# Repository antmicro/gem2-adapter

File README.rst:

GEM2 Adapter
============

Copyright (c) 2020 `Antmicro <https://www.antmicro.com>`_

.. image:: https://img.shields.io/badge/View%20on-Antmicro%20Open%20Source%20Portal-332d37?style=flat-square
      :target: https://github.com/antmicro/gem2-adapter
   
.. figure:: img/gem2-adapter.png

This repository contains PCB design files for an adapter board accommodating the GEM2 chip created jointly by `zGlue <http://zglue.com>`_ and `Antmicro <http://www.antmicro.com>`_.
The `GEM2 design <https://zglue.com/design-automation/oci/project/gem2>`_ utilizes the zGlue ZiP chiplet technology and has been prepared using zGlue's `ChipBuilder <http://chipbuilder.zglue.com/>`_ tool.
The design has been produced as a single integrated circuit in the LGA-96 package.

The GEM2 chip contains the following components located on a dynamically reconfigurable interposer:

* PicoRV32-based "Raven" RISC-V ASIC implementation (see `raven-picorv32 <https://github.com/efabless/raven-picorv32>`_ and associated resources)
* Lattice ``ICE40UP5K-UWG30ITR`` FPGA image processing
* 32Mbit SPI FLASH memory
* 12MHz system clock generator 
* Internal LDOs and power management unit maintaining 1V2, 1V8, 2V5, 3V3 system supplies

The chip is supplied from a single ``VUSB`` voltage of 5 VDC.
The board break-routes signals for MIPI Interfaces (Input and Output) along with Flash and FPGA programming pins and power supplies.

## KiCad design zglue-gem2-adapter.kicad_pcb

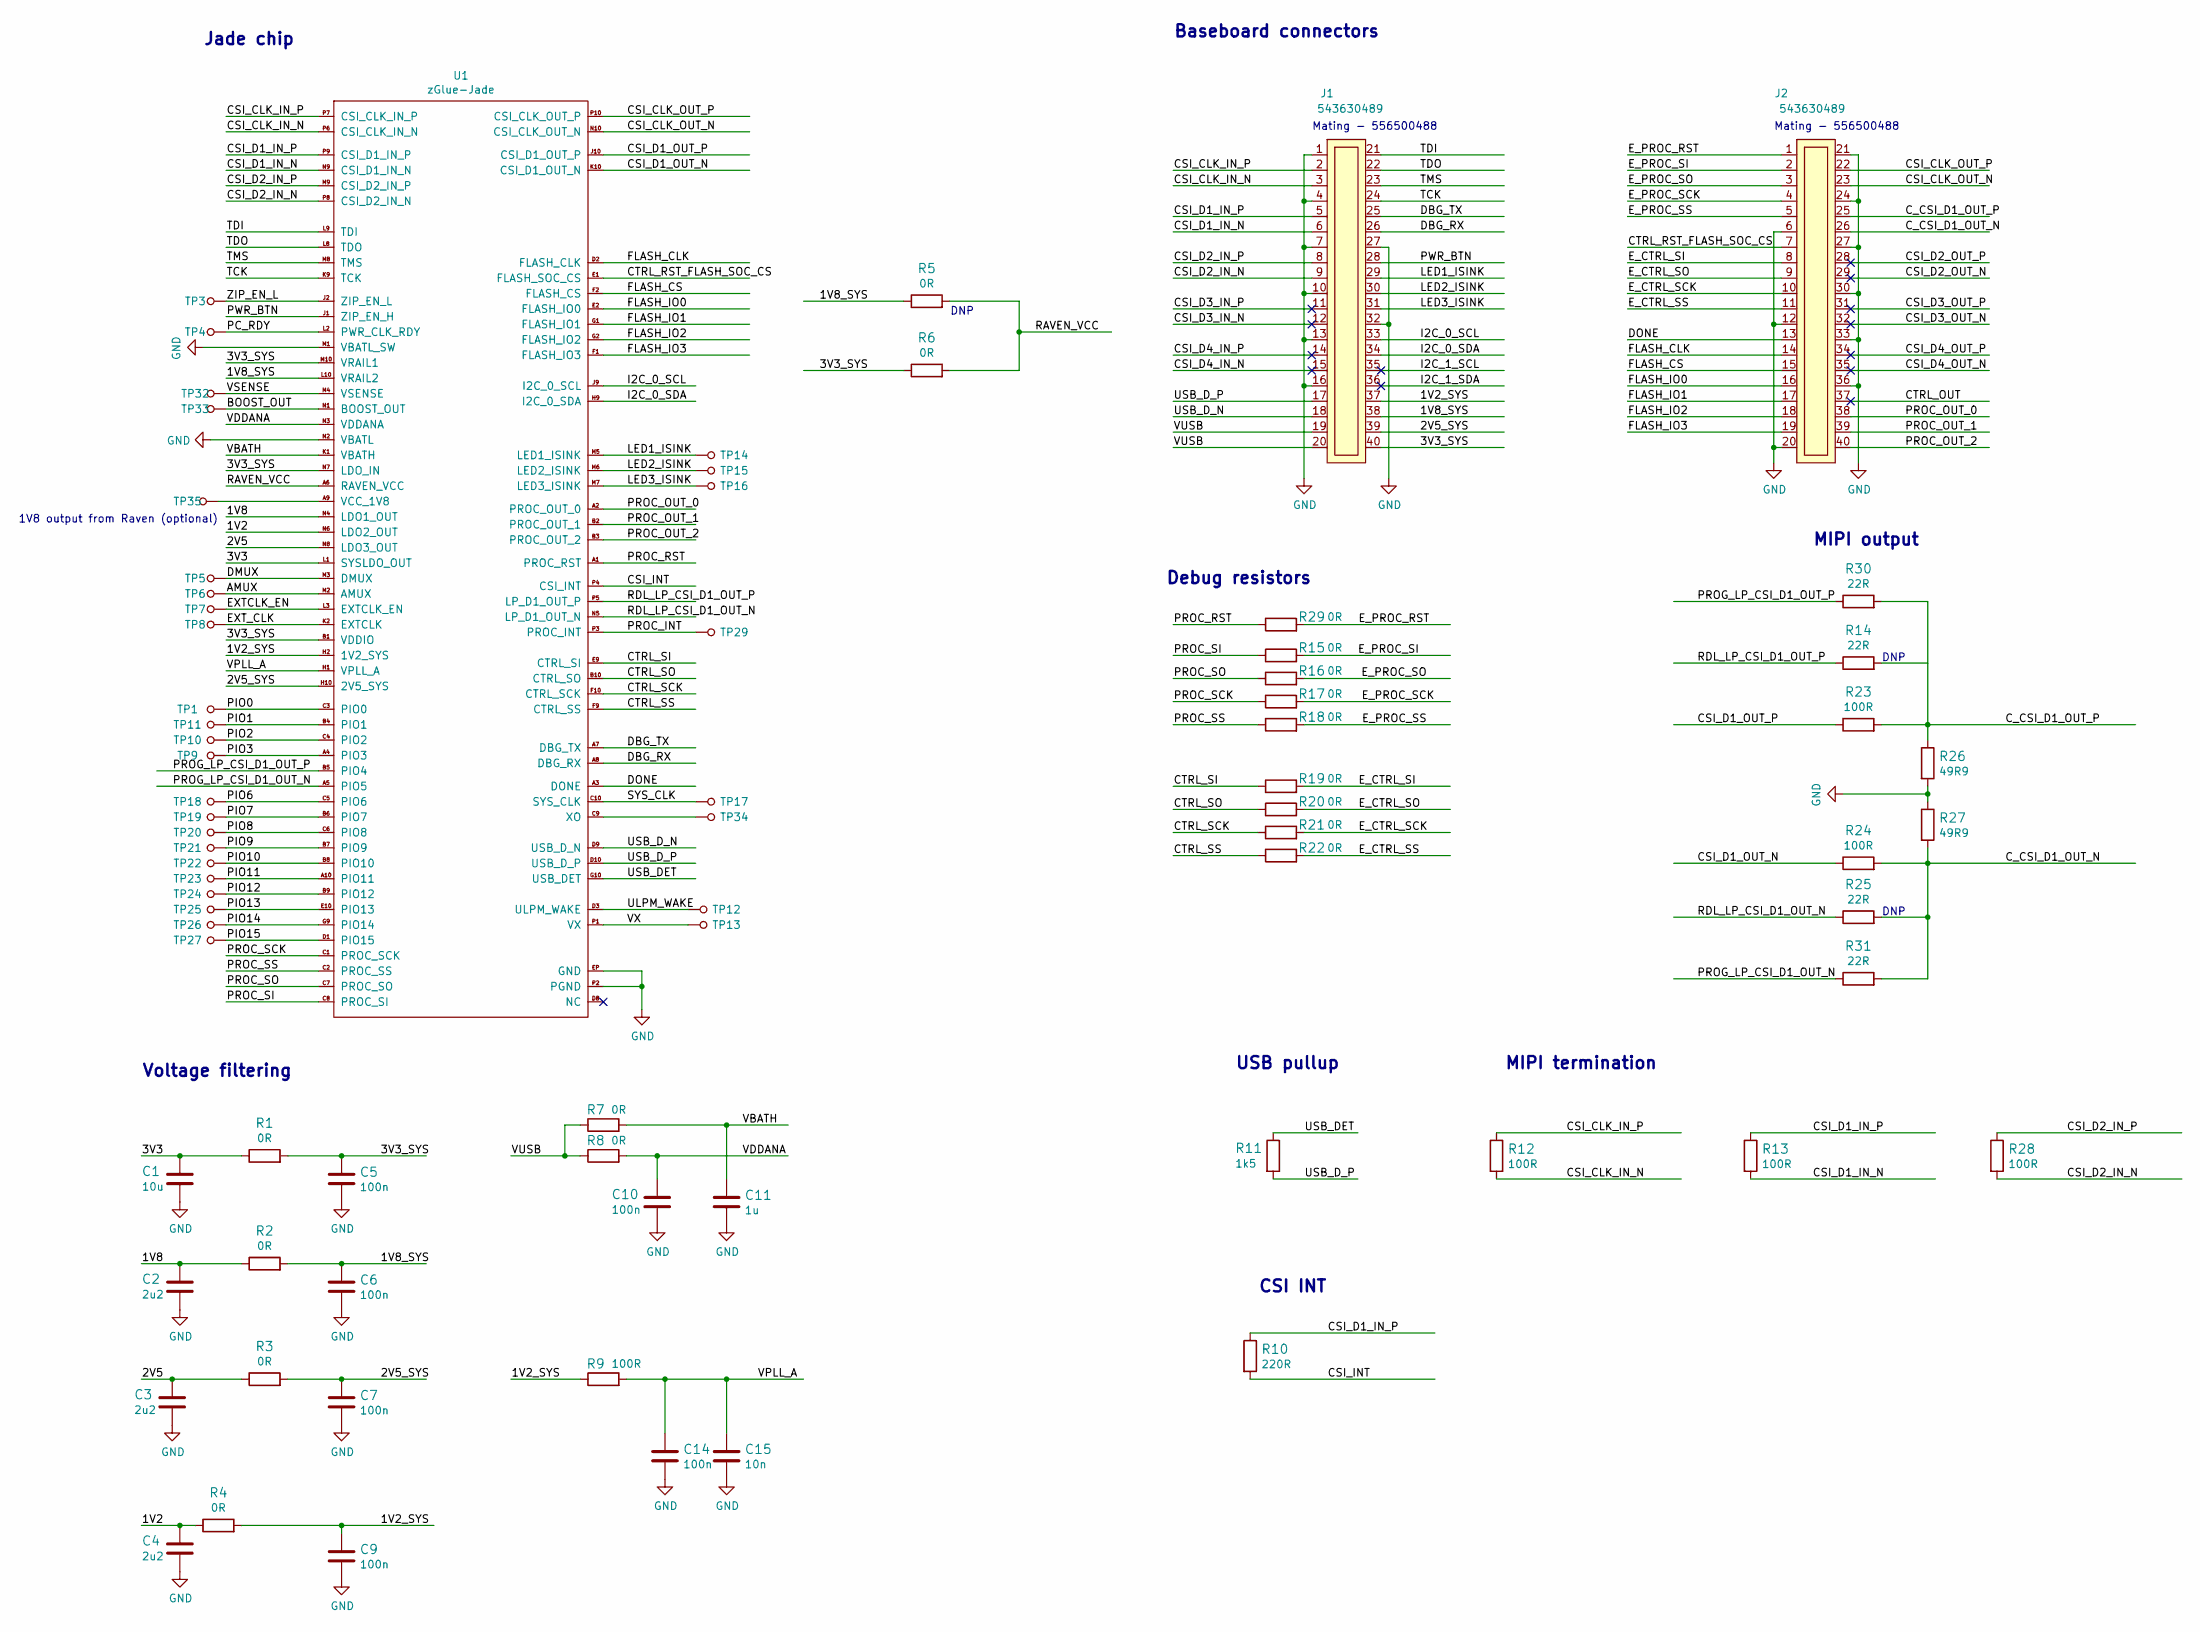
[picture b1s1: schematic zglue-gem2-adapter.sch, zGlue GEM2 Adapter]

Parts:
C1: C_10u_0402; 0402-cap; MPN C1005X5R0J106M050BC
C2, C3, C4: C_2u2_0402; 0402-cap; MPN C1005X5R1A225K050BC
C5, C6, C7, C9, C10, C14: C_100n_0402_6V3; 0402-cap; MPN 0402X104K6R3CT
C11: C_1u_0603; 0603-cap; MPN 0603X105K160CT
C15: C_10n_0402; 0402-cap; MPN 04025G103ZAT2A
J1, J2: 543630489; MPN 543630489
R1, R2, R3, R4, R5, R6, R7, R8, R15, R16, R17, R18, R19, R20, R21, R22, R29: R_0R_0402; 0402-res; MPN ERJ2GE0R00X
R9, R12, R13, R28: R_100R_0402; 0402-res; MPN CR0402-FX-1000GLF
R10: R_220R_0402; 0402-res; MPN CRG0402J220R
R11: R_1k5_0402; 0402-res; MPN ERJ2RKF1501X
R14, R25, R30, R31: R_22R_0402; 0402-res; MPN CRCW040222R0FKED
R23, R24: R_120R_0402; 0402-res; MPN CR0402-FX-1000GLF
R26, R27: R_49R9_0402; 0402-res; MPN CRCW040249R9FKED
TP1, TP3, TP4, TP5, TP6, TP7, TP8, TP9, TP10, TP11, TP12, TP13, TP14, TP15, TP16, TP17, TP18, TP19, TP20, TP21, TP22, TP23, TP24, TP25, TP26, TP27, TP29, TP32, TP33, TP34, TP35: TP_SMD1MM; Testpoint_smd_1mm
U1: zGlue-Jade; Z-Glue_LGA-96

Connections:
/1V2: C4.1, R4.1, U1.N6 (LDO2_OUT)
/1V2_SYS: C9.1, J1.37, R4.2, R9.1, U1.H2 (1V2_SYS)
/1V8: C2.1, R2.1, U1.N4 (LDO1_OUT)
/1V8_SYS: C6.1, J1.38, R2.2, R5.1, U1.L10 (VRAIL2)
/2V5: C3.1, R3.1, U1.N8 (LDO3_OUT)
/2V5_SYS: C7.1, J1.39, R3.2, U1.H10 (2V5_SYS)
/3V3: C1.1, R1.1, U1.L1 (SYSLDO_OUT)
/3V3_SYS: C5.1, J1.40, R1.2, R6.1, U1.B1 (VDDIO), U1.M10 (VRAIL1), U1.N7 (LDO_IN)
/AMUX: TP6.1, U1.M2 (AMUX)
/BOOST_OUT: TP33.1, U1.N1 (BOOST_OUT)
/CSI_CLK_IN_N: J1.3, R12.2, U1.P6 (CSI_CLK_IN_N)
/CSI_CLK_IN_P: J1.2, R12.1, U1.P7 (CSI_CLK_IN_P)
/CSI_CLK_OUT_N: J2.23, U1.N10 (CSI_CLK_OUT_N)
/CSI_CLK_OUT_P: J2.22, U1.P10 (CSI_CLK_OUT_P)
/CSI_D1_IN_N: J1.6, R13.2, U1.N9 (CSI_D1_IN_N)
/CSI_D1_IN_P: J1.5, R10.1, R13.1, U1.P9 (CSI_D1_IN_P)
/CSI_D1_OUT_N: R24.1, U1.K10 (CSI_D1_OUT_N)
/CSI_D1_OUT_P: R23.1, U1.J10 (CSI_D1_OUT_P)
/CSI_D2_IN_N: J1.9, R28.2, U1.P8 (CSI_D2_IN_N)
/CSI_D2_IN_P: J1.8, R28.1, U1.M9 (CSI_D2_IN_P)
/CSI_D2_OUT_N: J2.29
/CSI_D2_OUT_P: J2.28
/CSI_D3_IN_N: J1.12
/CSI_D3_IN_P: J1.11
/CSI_D3_OUT_N: J2.32
/CSI_D3_OUT_P: J2.31
/CSI_D4_IN_N: J1.15
/CSI_D4_IN_P: J1.14
/CSI_D4_OUT_N: J2.35
/CSI_D4_OUT_P: J2.34
/CSI_INT: R10.2, U1.P4 (CSI_INT)
/CTRL_OUT: J2.37
/CTRL_RST_FLASH_SOC_CS: J2.7, U1.E1 (FLASH_SOC_CS)
/CTRL_SCK: R21.1, U1.F10 (CTRL_SCK)
/CTRL_SI: R19.1, U1.E9 (CTRL_SI)
/CTRL_SO: R20.1, U1.B10 (CTRL_SO)
/CTRL_SS: R22.1, U1.F9 (CTRL_SS)
/C_CSI_D1_OUT_N: J2.26, R24.2, R25.2, R27.2, R31.2
/C_CSI_D1_OUT_P: J2.25, R14.2, R23.2, R26.1, R30.2
/DBG_RX: J1.26, U1.A8 (DBG_RX)
/DBG_TX: J1.25, U1.A7 (DBG_TX)
/DMUX: TP5.1, U1.M3 (DMUX)
/DONE: J2.13, U1.A3 (DONE)
/EXTCLK_EN: TP7.1, U1.L3 (EXTCLK_EN)
/EXT_CLK: TP8.1, U1.K2 (EXTCLK)
/E_CTRL_SCK: J2.10, R21.2
/E_CTRL_SI: J2.8, R19.2
/E_CTRL_SO: J2.9, R20.2
/E_CTRL_SS: J2.11, R22.2
/E_PROC_RST: J2.1, R29.2
/E_PROC_SCK: J2.4, R17.2
/E_PROC_SI: J2.2, R15.2
/E_PROC_SO: J2.3, R16.2
/E_PROC_SS: J2.5, R18.2
/FLASH_CLK: J2.14, U1.D2 (FLASH_CLK)
/FLASH_CS: J2.15, U1.F2 (FLASH_CS)
/FLASH_IO0: J2.16, U1.E2 (FLASH_IO0)
/FLASH_IO1: J2.17, U1.G1 (FLASH_IO1)
/FLASH_IO2: J2.18, U1.G2 (FLASH_IO2)
/FLASH_IO3: J2.19, U1.F1 (FLASH_IO3)
/I2C_0_SCL: J1.33, U1.J9 (I2C_0_SCL)
/I2C_0_SDA: J1.34, U1.H9 (I2C_0_SDA)
/I2C_1_SCL: J1.35
/I2C_1_SDA: J1.36
/LED1_ISINK: J1.29, TP14.1, U1.M5 (LED1_ISINK)
/LED2_ISINK: J1.30, TP15.1, U1.M6 (LED2_ISINK)
/LED3_ISINK: J1.31, TP16.1, U1.M7 (LED3_ISINK)
/PC_RDY: TP4.1, U1.L2 (PWR_CLK_RDY)
/PIO0: TP1.1, U1.C3 (PIO0)
/PIO1: TP11.1, U1.B4 (PIO1)
/PIO2: TP10.1, U1.C4 (PIO2)
/PIO3: TP9.1, U1.A4 (PIO3)
/PIO6: TP18.1, U1.C5 (PIO6)
/PIO7: TP19.1, U1.B6 (PIO7)
/PIO8: TP20.1, U1.C6 (PIO8)
/PIO9: TP21.1, U1.B7 (PIO9)
/PIO10: TP22.1, U1.B8 (PIO10)
/PIO11: TP23.1, U1.A10 (PIO11)
/PIO12: TP24.1, U1.B9 (PIO12)
/PIO13: TP25.1, U1.E10 (PIO13)
/PIO14: TP26.1, U1.G9 (PIO14)
/PIO15: TP27.1, U1.D1 (PIO15)
/PROC_INT: TP29.1, U1.P3 (PROC_INT)
/PROC_OUT_0: J2.38, U1.A2 (PROC_OUT_0)
/PROC_OUT_1: J2.39, U1.B2 (PROC_OUT_1)
/PROC_OUT_2: J2.40, U1.B3 (PROC_OUT_2)
/PROC_RST: R29.1, U1.A1 (PROC_RST)
/PROC_SCK: R17.1, U1.C1 (PROC_SCK)
/PROC_SI: R15.1, U1.C8 (PROC_SI)
/PROC_SO: R16.1, U1.C7 (PROC_SO)
/PROC_SS: R18.1, U1.C2 (PROC_SS)
/PROG_LP_CSI_D1_OUT_N: R31.1, U1.A5 (PIO5)
/PROG_LP_CSI_D1_OUT_P: R30.1, U1.B5 (PIO4)
/PWR_BTN: J1.28, U1.J1 (ZIP_EN_H)
/RAVEN_VCC: R5.2, R6.2, U1.A6 (RAVEN_VCC)
/RDL_LP_CSI_D1_OUT_N: R25.1, U1.N5 (LP_D1_OUT_N)
/RDL_LP_CSI_D1_OUT_P: R14.1, U1.P5 (LP_D1_OUT_P)
/SYS_CLK: TP17.1, U1.C10 (SYS_CLK)
/TCK: J1.24, U1.K9 (TCK)
/TDI: J1.21, U1.L9 (TDI)
/TDO: J1.22, U1.L8 (TDO)
/TMS: J1.23, U1.M8 (TMS)
/ULPM_WAKE: TP12.1, U1.D3 (ULPM_WAKE)
/USB_DET: R11.1, U1.G10 (USB_DET)
/USB_D_N: J1.18, U1.D9 (USB_D_N)
/USB_D_P: J1.17, R11.2, U1.D10 (USB_D_P)
/VBATH: C11.1, R7.2, U1.K1 (VBATH)
/VDDANA: C10.1, R8.2, U1.N3 (VDDANA)
/VPLL_A: C14.1, C15.1, R9.2, U1.H1 (VPLL_A)
/VSENSE: TP32.1, U1.M4 (VSENSE)
/VUSB: J1.19, J1.20, R7.1, R8.1
/VX: TP13.1, U1.P1 (VX)
/ZIP_EN_L: TP3.1, U1.J2 (ZIP_EN_L)
GND: C1.2, C2.2, C3.2, C4.2, C5.2, C6.2, C7.2, C9.2, C10.2, C11.2, C14.2, C15.2, J1.1, J1.4, J1.7, J1.10, J1.13, J1.16, J1.27, J1.32, J2.6, J2.12, J2.20, J2.21, J2.24, J2.27, J2.30, J2.33, J2.36, R26.2, R27.1, U1.EP (GND), U1.M1 (VBATL_SW), U1.N2 (VBATL), U1.P2 (PGND)
unnamed: TP34.1, U1.C9 (XO)
unnamed: TP35.1, U1.A9 (VCC_1V8)

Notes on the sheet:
Jade chip
Voltage filtering
Mating - 556500488
Baseboard connectors
Debug resistors
USB pullup
1V8 output from Raven (optional)
MIPI termination
CSI INT
MIPI output
DNP

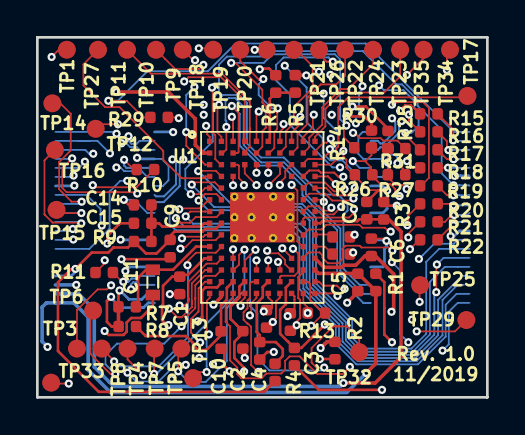
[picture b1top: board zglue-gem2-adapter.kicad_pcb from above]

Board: 6 copper layers, 25.0 x 20.0 mm, 77 parts (0 on the bottom side), 103 nets.

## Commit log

2020-05-29 Add component placement
2020-05-29 Add README
2020-05-29 Add LGA-96 step model, fix library links
2020-05-29 Rotate PCB by 180 deg to match chip logo orientation
2020-05-29 Move C1,2,3,4 closer to LDOs' outputs
2020-05-29 Modify LGA-96 thermal pad on paste layer
2020-05-29 Add initial layout
2020-05-29 Tune differential pairs
2020-05-29 Minor tweaks
2020-05-29 Add CSI_LP and CSI_INT signals and corresponding resistors
2020-05-29 Add 3D Vis to README
2020-05-29 Add DNP annotations
2020-05-29 Update pinout and layout
2020-05-29 Update the grid origin
2020-05-29 Add resistors for choosing CSI_LP signals connection
2020-05-29 Regenerate libraries
2020-05-29 Make more space on schematic sheet
2020-05-29 Update PCB
2020-05-29 Add logotype
2020-05-29 Update library naming
2020-05-29 Update GEM2 symbol
2020-05-29 README updates
2020-05-29 Review README
2020-05-29 Update PDF schematic
2020-10-01 Update photo
2020-10-01 Add OCI link
2020-10-01 Fix path
2021-06-24 Notes added by 'git notes add'
2022-05-27 Scale image
2022-05-27 Add badge
